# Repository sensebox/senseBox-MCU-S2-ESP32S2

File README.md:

# senseBoxMCU-S2 ESP32S2

# Erste Schritte

## Vorbereitung der Arduino IDE
Für den ESP32 werden von der Arduino-DIE zusätzliche Repositories benötigt:
Unter Datei -> Voreinstellungen muss unter Zusätzliche Boardverwalter-URLs 
```
https://raw.githubusercontent.com/espressif/arduino-esp32/gh-pages/package_esp32_dev_index.json
```
eingetragen werden. Anschließend muss unter Werkzeuge  Board: …  Boardverwalter… das Tool esp32 by Espressif Systems installiert werden.
Nachdem alles geladen wurde, muss man unter Werkzeuge das Board ESP32S2 Dev Module auswählen und USB CDC On Boot auf Enable stellen.
Zur Nutzung des UF2-Bootloaders müssen die UF2-Dateien von der Arduino-DIE erzeugt werden. Eine ausführliche Anleitung, wie die Arduino-IDE hierfür angepasst werden muss, findet sich unter
https://blog.adafruit.com/2021/09/17/automated-generation-of-bin-hex-uf2-files-for-arduino-continuous-integration/

### Installieren des UF2-Bootloaders
Eine Anleitung zur Installation des UF2-Bootloaders findet sich unter:
https://learn.adafruit.com/adafruit-metro-esp32-s2/install-uf2-bootloader

### Demo Codes

**Abstandssensor**
Es wird aus der Arduino-Bibliothek das Bifrost library for HC-SR04 Modul benötigt.
Es handelt sich hier um das angepasste Beispiel aus dem Modul, hier wurden lediglich die Pins für den IO2/IO3 Stecker angepasst und das Aktivieren der IO-Ports hinzugefügt.

**GPIO** 
Es werden keine besonderen Module benötigt.
Im Code werden die IO-Ports aktiviert und die beiden GPIOs 6 und 7 im Sekundentakt ein- und ausgeschaltet.

**IMU-Sensor ICM-20948**
Es wird zusätzlich das ICM20948_WE Modul benötigt
Dies ist das angepasste Modul aus der Beispielsammlung. Es wurden die I2C-IOs angepasst.

**Lichtsensor / Photo-Diode**
In diesem Beispiel wird die fest verbaute IN-S63DTLS analog gemessen. Besonders hier ist hier, dass PD_ENABLE Active-High ist, anstatt Active-Low wie in den anderen Beispielen.
Die Photodiode wird einmal pro Sekunde gemessen und der Bytewert ist über den seriellen Monitor von Arduino ausgebbar.
Die gemessene Spannung ist abhängig vom Photostrom der Photodiode:
V_Out=I_Photo/R
mit 
R=33kΩ
Bei normalem Umgebungslicht sollte der Bytewert etwa 200-500 betragen, bei direkter Sonneneinstrahlung liegt der Wert typisch bei 1000-2000. Bei direkter Bestrahlung mit einer weißen Hochleistungs-LED kann der Wert bis zum maximalen Wert von 4095 steigen. Die folgende Abbildung aus dem Datenblatt der Photodiode zeigt den Zusammenhang zwischen Lichtintensität und Photostrom:

**RGB-LED**
Es wird zusätzlich das Freenove_WS2812_Lib_for_ESP32 Modul benötigt.
Dieses Beispiel lässt die verbaute WS2812-LED im Sekundentakt alternativ rot, grün oder blau leuchten.

**SD-Card**
Das SD-Modul ist automatisch installiert.
Dieses ist das angepasste Beispiel aus dem Modul, es wurde die Aktivierung der Stromversorgung der SD-Karte hinzugefügt. Zusätzlich mussten die GPIOs für SPI angepasst werden.

**WLAN Client**
Das genutzte Wifi Modul ist automatisch installiert. 
Dieses Beispiel versucht eine WLAN-Verbindung aufzubauen und dann einen Webserver zu erreichen.

## Reset Button 
Das Board kann zurück in den Bootloader Modus gebracht werden, wenn der `Reset` Knopf gedrückt wird und der `Boot-Switch`-Button gleichzeitig gehalten wird.

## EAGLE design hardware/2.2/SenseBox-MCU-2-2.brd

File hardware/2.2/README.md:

The following should be noted regarding these schematics:
- The chip name is  actually "ESP32-S2-MINI-1-N4R2"
- The UART_ENABLE Pin is not used anymore for enabeling the UART (UART is always enabled now). It is instead used internally for the PSRAM

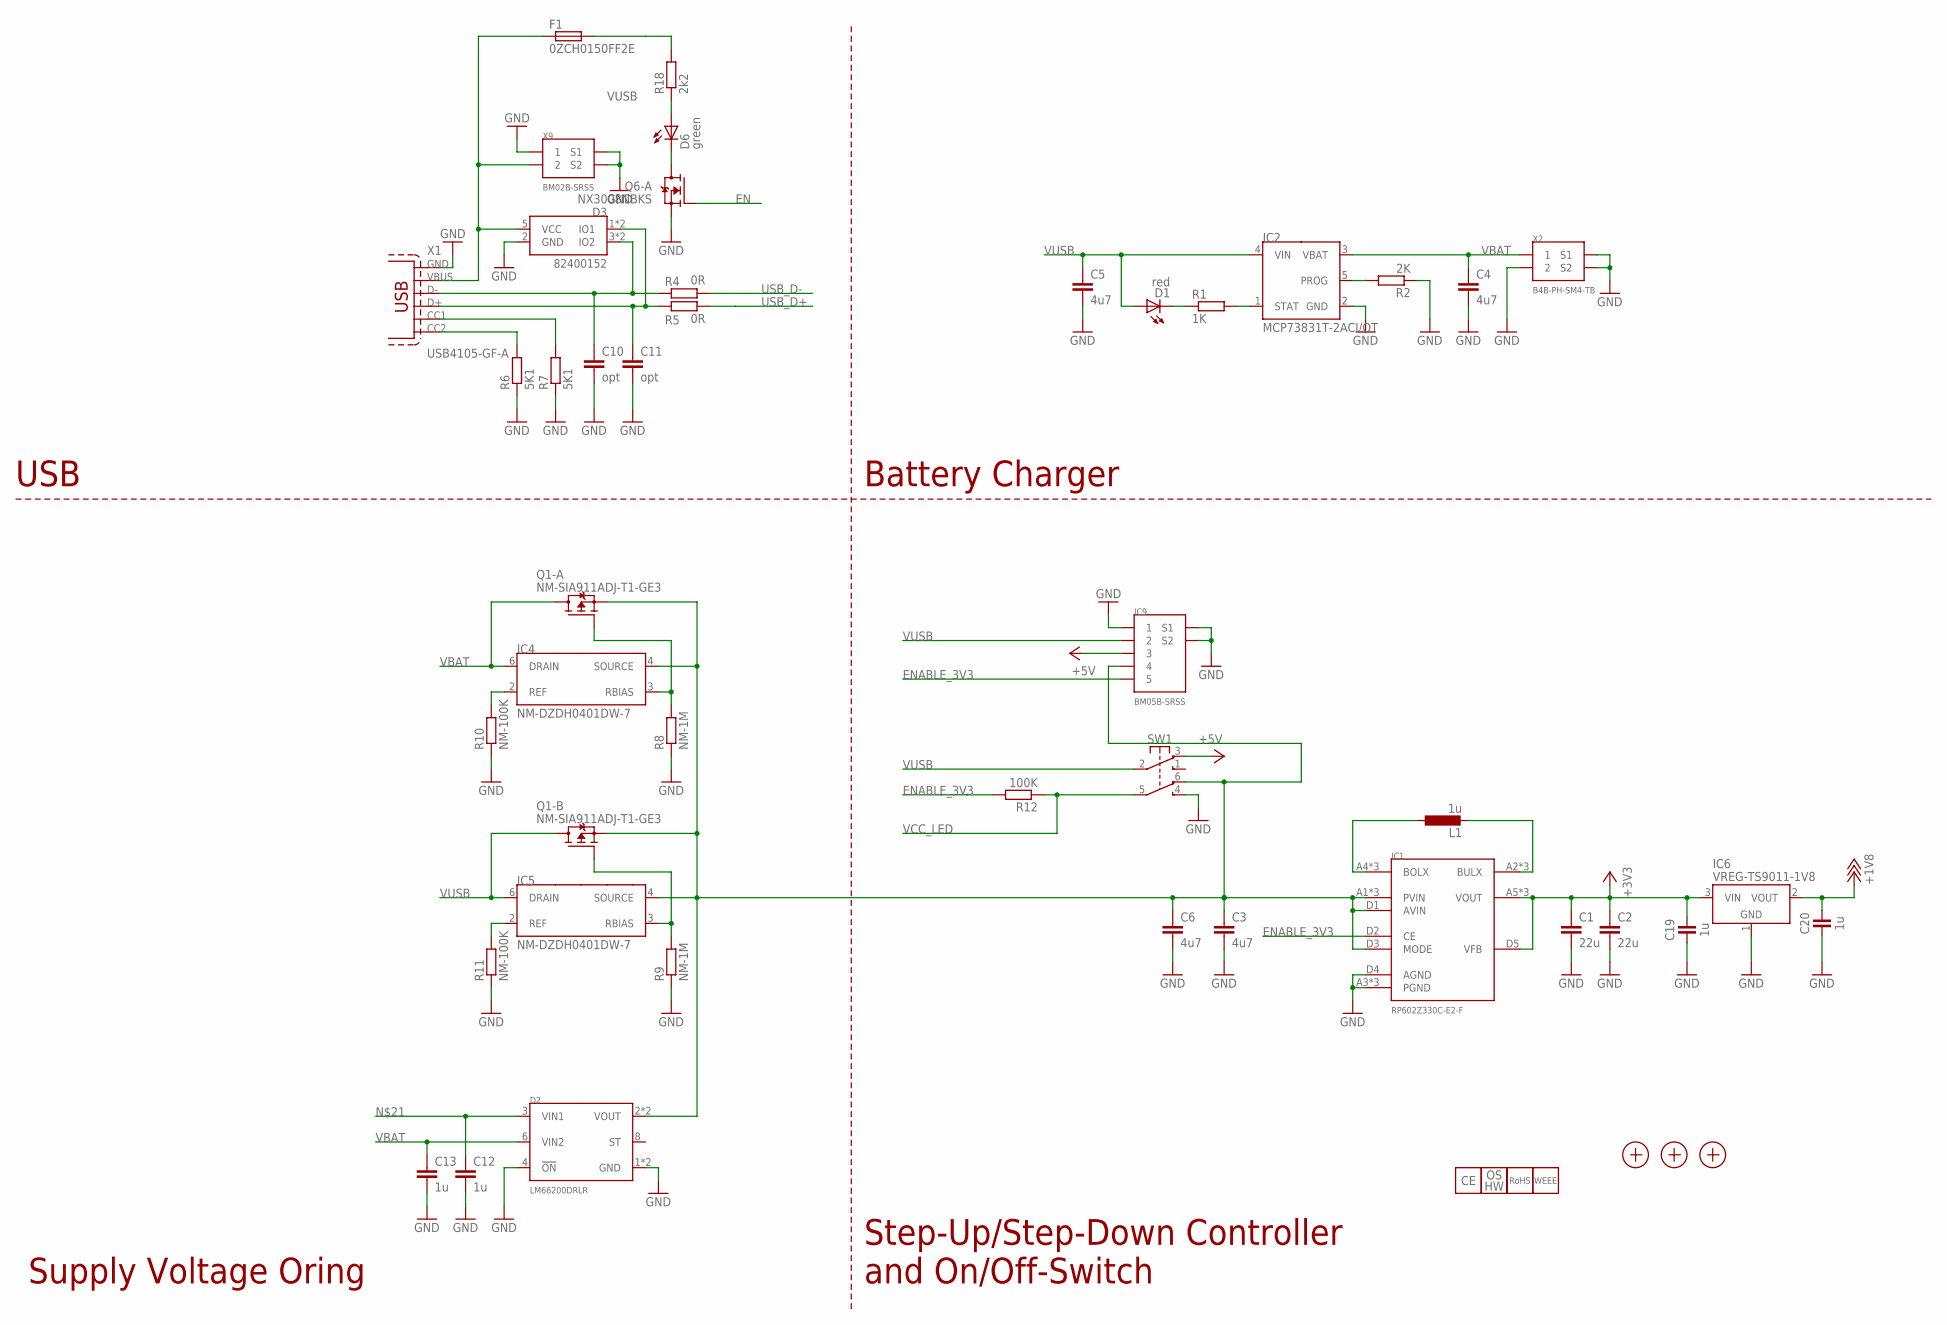
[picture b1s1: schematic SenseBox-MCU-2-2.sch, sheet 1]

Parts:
C1, C2: 22u; 0805N
C3, C4, C5, C6: 4u7; 0603N
C10, C11: opt; 0402N
C12, C13: 1u; 0402N
C19, C20: 1u; C0402
D1: red; 0603N
D2: LM66200DRLR; SOT-5X3
D3: 82400152; SOT563
D6: green; 0603N
F1: 0ZCH0150FF2E; 1210N
IC1: RP602Z330C-E2-F; WLCSP-20-P1
IC2: MCP73831T-2ACI/OT; SOT23-5
IC4, IC5: NM-DZDH0401DW-7; SOT363
IC6: VREG-TS9011-1V8; SOT23
IC9: BM05B-SRSS
L1: 1u; 5040
LOGO1: LOGO_CE-2; CE_2MM
LOGO2: LOGO_OSHW-2; OSHW_2MM
LOGO3: LOGO_ROHS-2; ROHS_2MM
LOGO4: LOGO_WEEE-4; WEEE_4MM
Q1: NM-SIA911ADJ-T1-GE3; POWERPAK-SC70-6
Q6: NX3008NBKS; SOT363
R1: 1K; 0402N
R2: 2K; 0402N
R4, R5: 0R; 0402N
R6, R7: 5K1; 0402N
R8, R9: NM-1M; 0402N
R10, R11: NM-100K; 0402N
R12: 100K; 0402N
R18: 2k2; 0402N
SW1: SW-2UM-CUS22B; CUS22B
X1: USB4105-GF-A; USB4105
X2: B4B-PH-SM4-TB
X9: BM02B-SRSS
X13, X14, X15: PASSER-07; PASSER_07MM

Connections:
+1V8: C20.2, IC6.2 (VOUT); also elsewhere on the board
+3V3: C1.1, C2.1, C19.2, IC1.A5 (VOUT), IC1.B5 (VOUT), IC1.C5 (VOUT), IC1.D5 (VFB), IC6.3 (VIN); also elsewhere on the board
+5V: IC9.3, SW1.3 (NC1)
EN: Q6.2 (G); also elsewhere on the board
ENABLE_3V3: IC1.D2 (CE), IC9.5, R12.2
GND: C1.2, C2.2, C3.2, C4.2, C5.2, C6.2, C10.2, C11.2, C12.2, C13.2, C19.1, C20.1, D2.1 (GND), D2.4 (!ON), D2.5 (GND), D3.2 (GND), IC1.A3 (PGND), IC1.B3 (PGND), IC1.C3 (PGND), IC1.D4 (AGND), IC2.2 (GND), IC6.1 (GND), IC9.1, IC9.S1, IC9.S2, Q6.1 (S), R2.1, R6.1, R7.1, R8.1, R9.1, R10.1, R11.1, SW1.4 (NO2), X1.A1_B12 (GND), X1.B1_A12 (GND), X1.S1 (GND), X1.S2 (GND), X1.S3 (GND), X1.S4 (GND), X2.2, X2.SH1 (S1), X2.SH2 (S2), X9.1, X9.S1, X9.S2; also elsewhere on the board
unnamed: IC1.A4 (BOLX), IC1.B4 (BOLX), IC1.C4 (BOLX), L1.1
unnamed: IC1.A2 (BULX), IC1.B2 (BULX), IC1.C2 (BULX), L1.2
unnamed: IC2.5 (PROG), R2.2
unnamed: IC4.2 (REF), R10.2
unnamed: D1.C, R1.1
unnamed: IC2.1 (STAT), R1.2
unnamed: C10.1, D3.3 (IO2), D3.4 (IO2), R4.1, X1.A7 (D-), X1.B7 (D-)
unnamed: C11.1, D3.1 (IO1), D3.6 (IO1), R5.1, X1.A6 (D+), X1.B6 (D+)
unnamed: R6.2, X1.B5 (CC2)
unnamed: R7.2, X1.A5 (CC1)
unnamed: D3.5 (VCC), F1.1 (2), X1.A4_B9 (VBUS), X1.B4_A9 (VBUS), X9.2
unnamed: IC5.2 (REF), R11.2
unnamed: IC4.3 (RBIAS), Q1.2 (G), R8.2
unnamed: C3.1, C6.1, D2.2 (VOUT), D2.7 (VOUT), IC1.A1 (PVIN), IC1.B1 (PVIN), IC1.C1 (PVIN), IC1.D1 (AVIN), IC1.D3 (MODE), IC4.4 (SOURCE), IC5.4 (SOURCE), IC9.4, Q1.1 (S), Q1.4 (S), SW1.6 (NC2)
unnamed: IC5.3 (RBIAS), Q1.5 (G), R9.2
unnamed: C12.1, D2.3 (VIN1)
unnamed: D6.A, R18.1
unnamed: D6.C, Q6.6 (D)
USB_D+: R5.2; also elsewhere on the board
USB_D-: R4.2; also elsewhere on the board
VBAT: C4.1, C13.1, D2.6 (VIN2), IC2.3 (VBAT), IC4.6 (DRAIN), Q1.6 (D), Q1.7 (D), X2.1
VCC_LED: R12.1, SW1.5 (C2); also elsewhere on the board
VUSB: C5.1, D1.A, F1.2 (3), IC2.4 (VIN), IC5.6 (DRAIN), IC9.2, Q1.3 (D), Q1.8 (D), R18.2, SW1.2 (C1)

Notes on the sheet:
USB
Battery Charger
Supply Voltage Oring
Step-Up/Step-Down Controller and On/Off-Switch

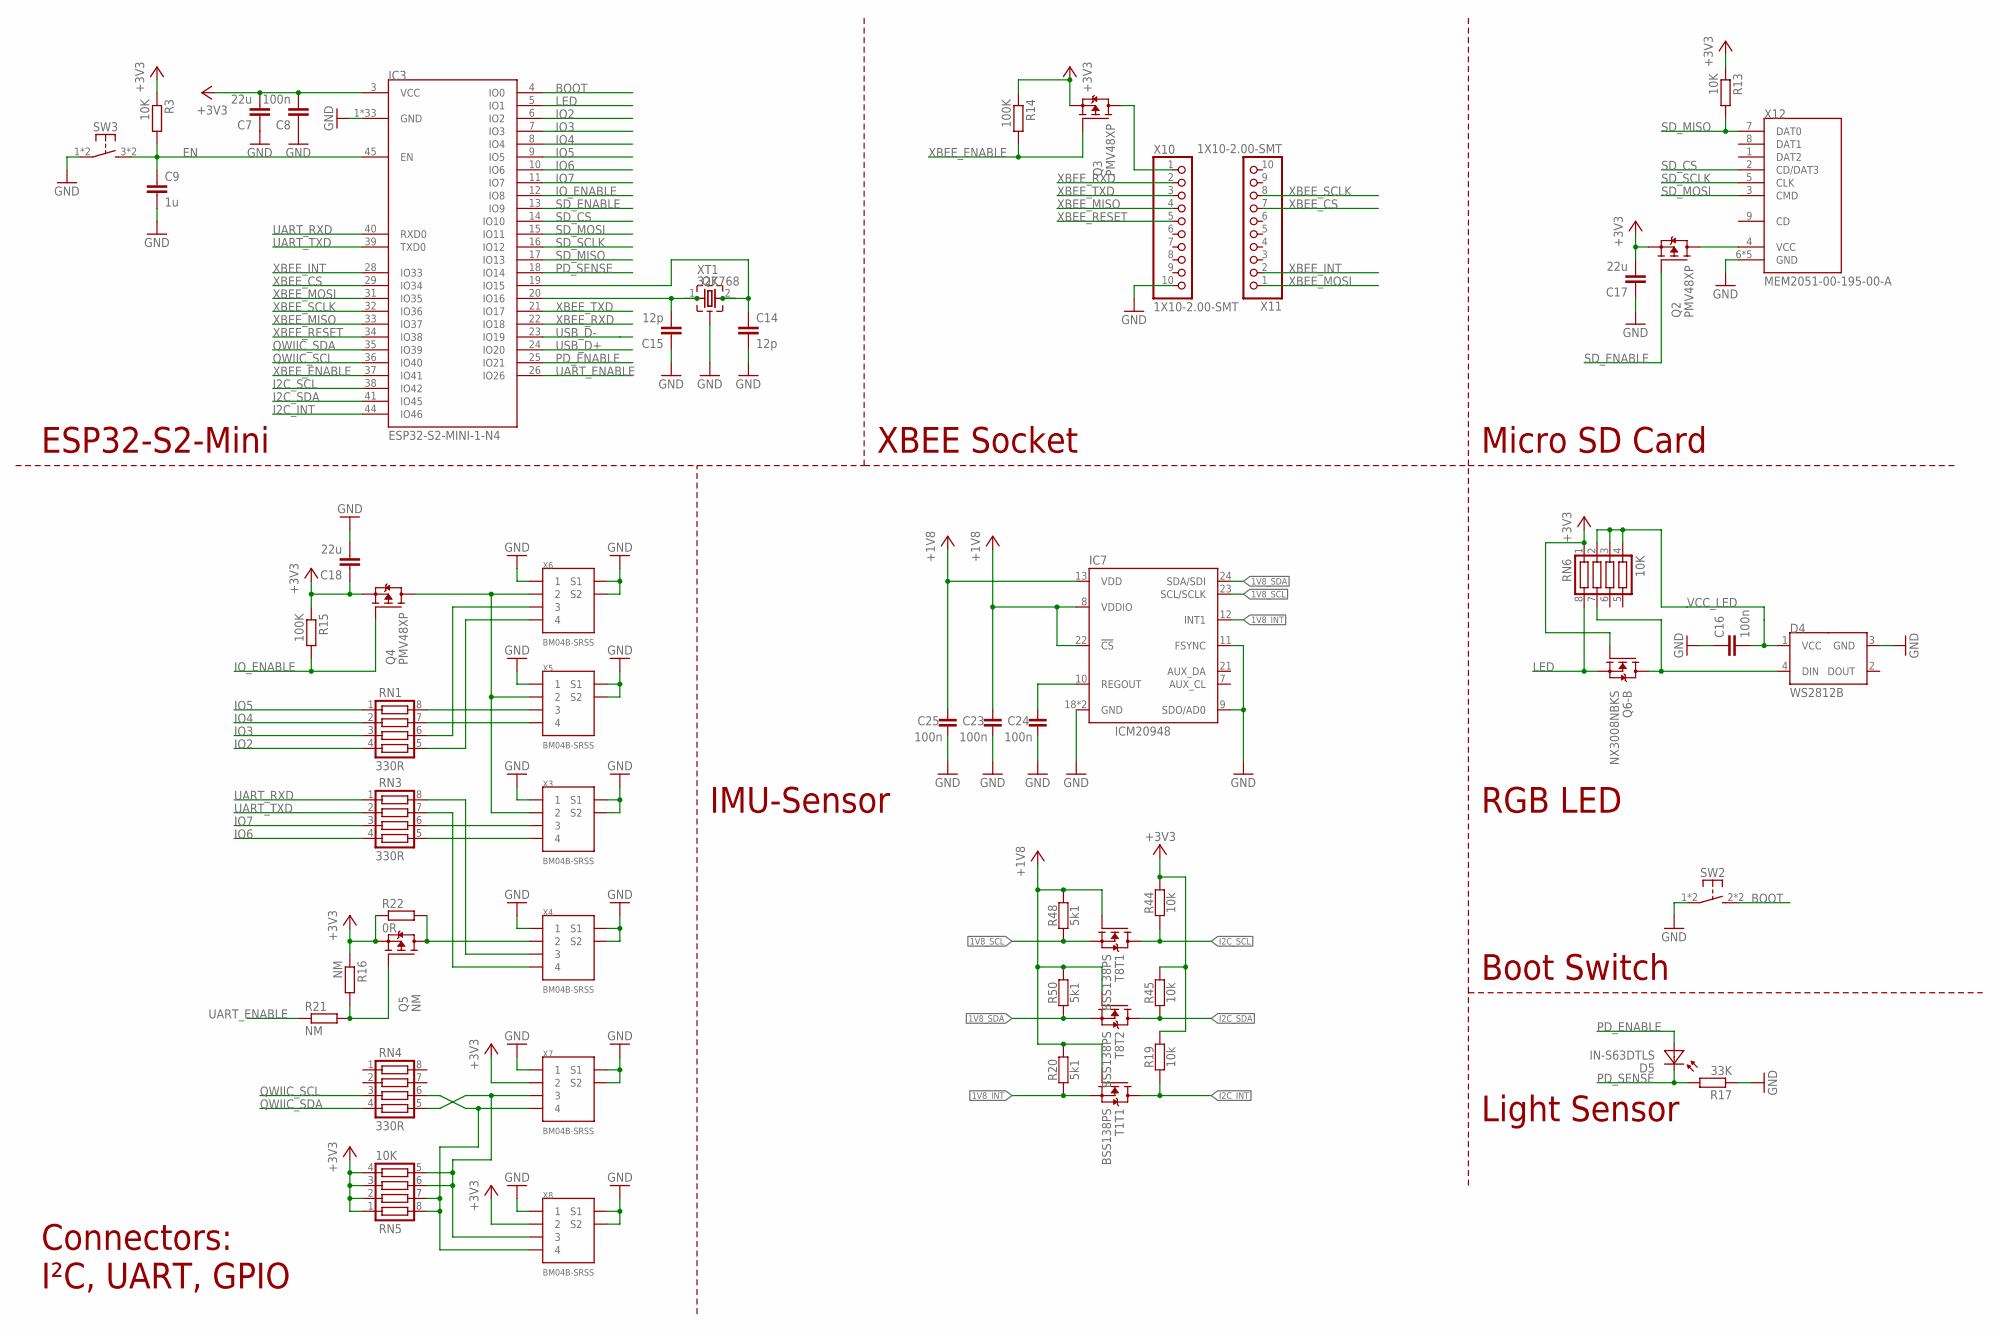
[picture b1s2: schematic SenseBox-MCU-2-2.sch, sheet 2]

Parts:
C7, C17, C18: 22u; 0805N
C8, C16: 100n; 0402N
C9: 1u; 0402N
C14, C15: 12p; 0402N
C23, C24, C25: 100n; C0402
D4: WS2812B; 5050
D5: IN-S63DTLS; 0603N
IC3: ESP32-S2-MINI-1-N4; ESP32-S2-MINI
IC7: ICM20948; QFN24-3X3
Q2, Q3, Q4: PMV48XP; SOT23
Q5: NM; SOT23
Q6: NX3008NBKS; SOT363
Q7: CRYSTAL-ZM315; CRYSTAL_ZM315
R3, R13: 10K; 0402N
R14, R15: 100K; 0402N
R16, R21: NM; 0402N
R17: 33K; 0402N
R19, R44, R45: 10k; C0402
R20, R48, R50: 5k1; C0402
R22: 0R; 0402N
RN1, RN3, RN4: 330R; CAY16
RN5, RN6: 10K; CAY16
SW2: SW-TACTILE-TL3365; TL3365
SW3: SW-TACTILE-PTS840P; PTS840P
T1, T8: BSS138PS; SOT363
X3, X4, X5, X6, X7, X8: BM04B-SRSS
X10, X11: 1X10-2.00-SMT; 1X10-2.00-SMD
X12: MEM2051-00-195-00-A; MEM2051
XT1: 32K768; 1.4X1.5X5.2

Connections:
1V8_INT: IC7.12 (INT1), R20.1, T1.1 (S)
1V8_SCL: IC7.23 (SCL/SCLK), R48.1, T8.1 (S)
1V8_SDA: IC7.24 (SDA/SDI), R50.1, T8.4 (S)
+1V8: C23.2, C25.2, IC7.8 (VDDIO), IC7.13 (VDD), IC7.22 (!CS), R20.2, R48.2, R50.2, T1.2 (G), T8.2 (G), T8.5 (G); also elsewhere on the board
+3V3: C7.2, C8.2, C17.2, C18.1, IC3.3 (VCC), Q2.2 (S), Q3.2 (S), Q4.2 (S), Q5.2 (S), Q6.5 (G), R3.1, R13.1, R14.1, R15.1, R16.1, R19.2, R22.1, R44.2, R45.2, RN5.1, RN5.2, RN5.3, RN5.4, RN6.1, X7.2, X8.2; also elsewhere on the board
BOOT: IC3.4 (IO0), SW2.2 (S1), SW2.3 (S1)
EN: C9.1, IC3.45 (EN), R3.2, SW3.3 (S1), SW3.4 (S1); also elsewhere on the board
GND: C7.1, C8.1, C9.2, C14.2, C15.1, C16.1, C17.1, C18.2, C23.1, C24.1, C25.1, D4.3 (GND), IC3.1 (GND), IC3.2 (GND), IC3.30 (GND), IC3.42 (GND), IC3.43 (GND), IC3.46 (GND), IC3.47 (GND), IC3.48 (GND), IC3.49 (GND), IC3.50 (GND), IC3.51 (GND), IC3.52 (GND), IC3.53 (GND), IC3.54 (GND), IC3.55 (GND), IC3.56 (GND), IC3.57 (GND), IC3.58 (GND), IC3.59 (GND), IC3.60 (GND), IC3.61 (GND), IC3.62 (GND), IC3.63 (GND), IC3.64 (GND), IC3.65 (GND), IC3.66 (GND), IC3.67 (GND), IC3.68 (GND), IC3.69 (GND), IC3.70 (GND), IC3.71 (GND), IC3.72 (GND), IC3.73 (GND), IC7.9 (SDO/AD0), IC7.11 (FSYNC), IC7.18 (GND), IC7.20 (GND), R17.1, SW2.1, SW2.4 (P1), SW3.1, SW3.2 (P1), X3.1, X3.S1, X3.S2, X4.1, X4.S1, X4.S2, X5.1, X5.S1, X5.S2, X6.1, X6.S1, X6.S2, X7.1, X7.S1, X7.S2, X8.1, X8.S1, X8.S2, X10.10, X12.6 (GND), X12.S1 (GND), X12.S2 (GND), X12.S3 (GND), X12.S4 (GND), XT1.3 (GND); also elsewhere on the board
I2C_INT: IC3.44 (IO46), R19.1, T1.6 (D)
I2C_SCL: IC3.38 (IO42), R44.1, T8.6 (D)
I2C_SDA: IC3.41 (IO45), R45.1, T8.3 (D)
IO2: IC3.6 (IO2), RN1.4
IO3: IC3.7 (IO3), RN1.3
IO4: IC3.8 (IO4), RN1.2
IO5: IC3.9 (IO5), RN1.1
IO6: IC3.10 (IO6), RN3.4
IO7: IC3.11 (IO7), RN3.3
IO_ENABLE: IC3.12 (IO8), Q4.1 (G), R15.2
LED: IC3.5 (IO1), Q6.4 (S), RN6.8
unnamed: RN1.6, X6.3
unnamed: C15.2, IC3.20 (IO16), Q7.1, XT1.1
unnamed: C14.1, IC3.19 (IO15), Q7.2, XT1.2
unnamed: D4.4 (DIN), Q6.3 (D), RN6.7
unnamed: Q4.3 (D), X3.2, X5.2, X6.2
unnamed: Q2.3 (D), X12.4 (VCC)
unnamed: Q3.3 (D), X10.1
unnamed: Q5.3 (D), R22.2, X4.2
unnamed: RN1.5, X6.4
unnamed: RN1.8, X5.3
unnamed: RN1.7, X5.4
unnamed: RN3.5, X3.4
unnamed: RN3.6, X3.3
unnamed: RN3.8, X4.3
unnamed: RN3.7, X4.4
unnamed: RN4.6, RN5.7, RN5.8, X7.4, X8.4
unnamed: RN4.5, RN5.5, RN5.6, X7.3, X8.3
PD_ENABLE: D5.A, IC3.25 (IO21)
PD_SENSE: D5.C, IC3.18 (IO14), R17.2
QWIIC_SCL: IC3.36 (IO40), RN4.3
QWIIC_SDA: IC3.35 (IO39), RN4.4
REGOUT1: C24.2, IC7.10 (REGOUT)
SD_CS: IC3.14 (IO10), X12.2 (CD/DAT3)
SD_ENABLE: IC3.13 (IO9), Q2.1 (G)
SD_MISO: IC3.17 (IO13), R13.2, X12.7 (DAT0)
SD_MOSI: IC3.15 (IO11), X12.3 (CMD)
SD_SCLK: IC3.16 (IO12), X12.5 (CLK)
UART_ENABLE: IC3.26 (IO26), R21.1
UART_ENABLE1: Q5.1 (G), R16.2, R21.2
UART_RXD: IC3.40 (RXD0), RN3.1
UART_TXD: IC3.39 (TXD0), RN3.2
USB_D+: IC3.24 (IO20); also elsewhere on the board
USB_D-: IC3.23 (IO19); also elsewhere on the board
VCC_LED: C16.2, D4.1 (VCC), RN6.2, RN6.3, RN6.4; also elsewhere on the board
XBEE_CS: IC3.29 (IO34), X11.7
XBEE_ENABLE: IC3.37 (IO41), Q3.1 (G), R14.2
XBEE_INT: IC3.28 (IO33), X11.2
XBEE_MISO: IC3.33 (IO37), X10.4
XBEE_MOSI: IC3.31 (IO35), X11.1
XBEE_RESET: IC3.34 (IO38), X10.5
XBEE_RXD: IC3.22 (IO18), X10.2
XBEE_SCLK: IC3.32 (IO36), X11.8
XBEE_TXD: IC3.21 (IO17), X10.3

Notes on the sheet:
Connectors: I²C, UART, GPIO
IMU-Sensor
Light Sensor
Boot Switch
XBEE Socket
Micro SD Card
ESP32-S2-Mini
RGB LED

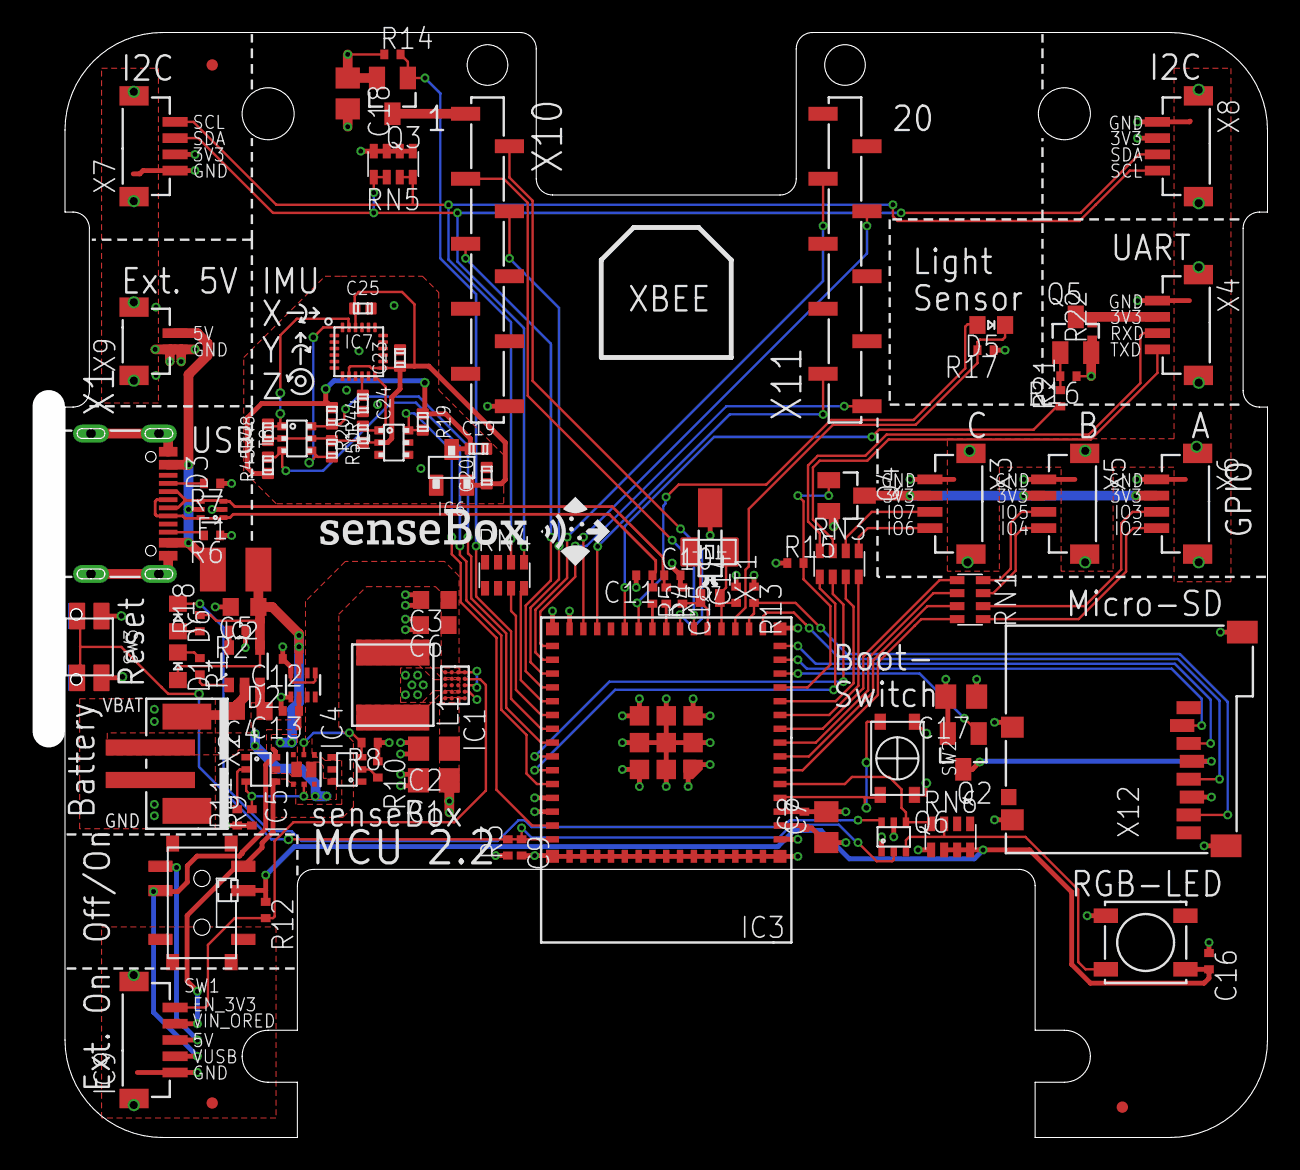
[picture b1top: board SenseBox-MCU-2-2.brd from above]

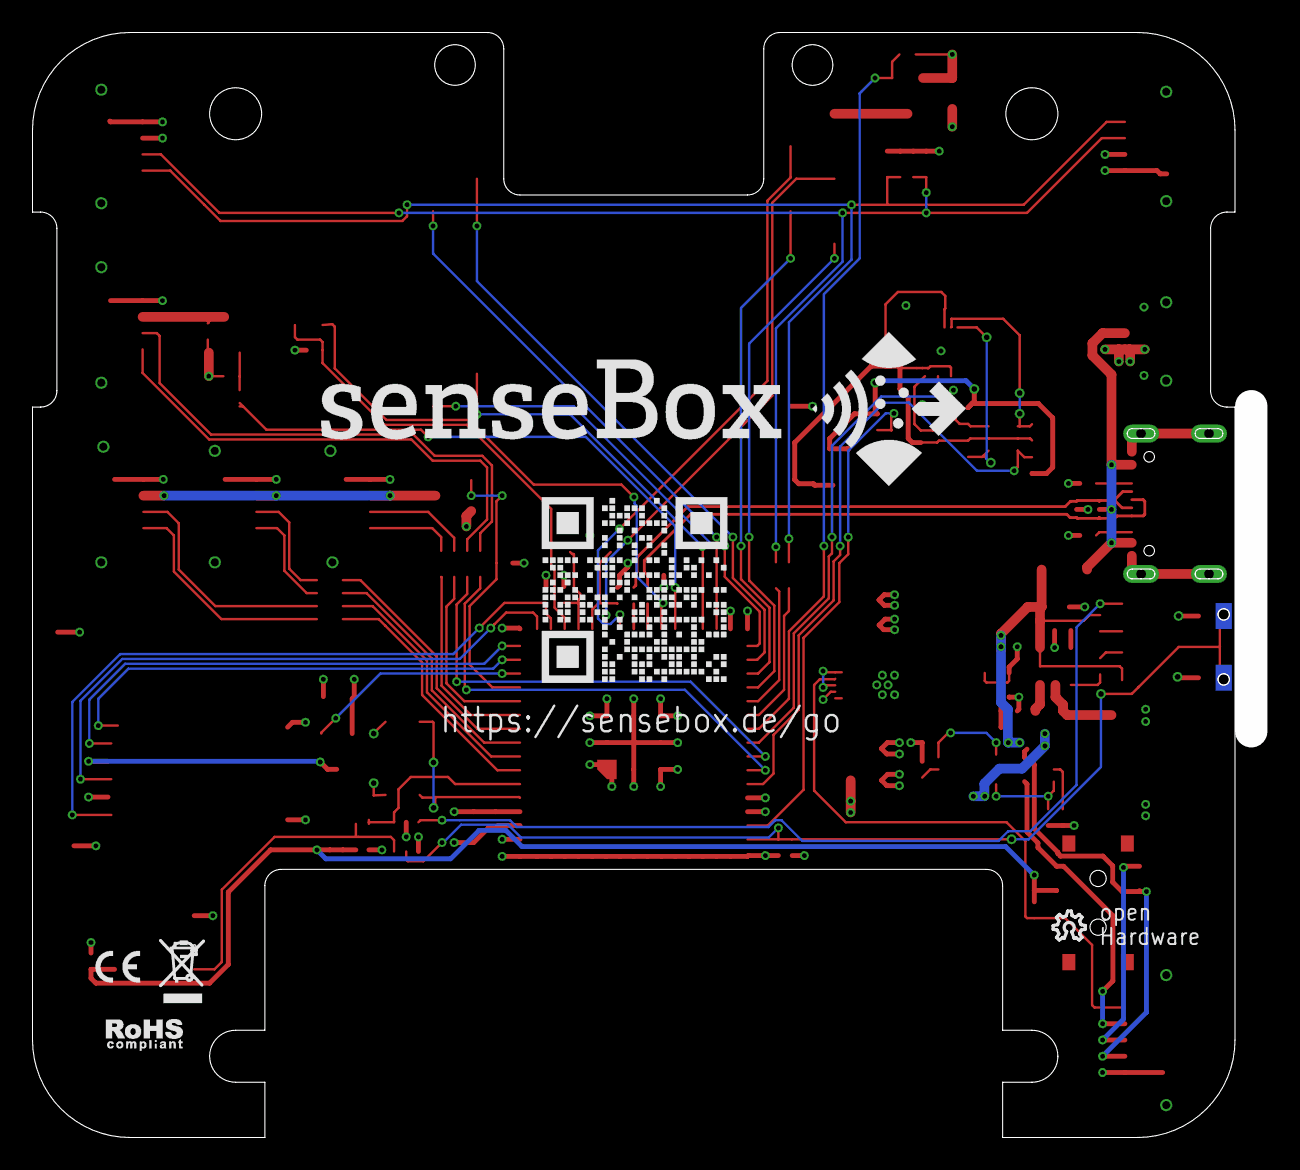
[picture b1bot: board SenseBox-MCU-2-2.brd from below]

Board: 4 copper layers, 74.0 x 66.0 mm, 102 parts (4 on the bottom side), 84 nets.

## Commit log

2023-08-17 add examples, hardwarefiles and first doku
2023-10-11 update the mpu6050 example (new library)
2023-10-17 add 2.1 schematics pdf
2023-10-25 vl53l8cx with led matrix example
2023-10-25 increase ranging frequency
2023-11-09 add sleep+wakeup example
2023-12-12 add initialization sketch
2023-12-18 Update SMT50.ino
    Fix reference voltage by using analogReadMilliVolts and set read resolution to 13bit.
2024-01-09 add rtc example
2024-02-19 led matrix: generated fire example
2024-03-13 Moved SPSI init
    ...because if its just init in setup it will get destroyed and using any sd funciton such as "readFile" in the loop will break the esp
2024-04-16 add home v2 sketch version [beta]
2024-04-16 renamed folders
2024-11-14 update vl53l8cx code
2025-05-13 add example for icm42670P
2025-06-23 add 2.2 schematics
2025-06-24 add readme
